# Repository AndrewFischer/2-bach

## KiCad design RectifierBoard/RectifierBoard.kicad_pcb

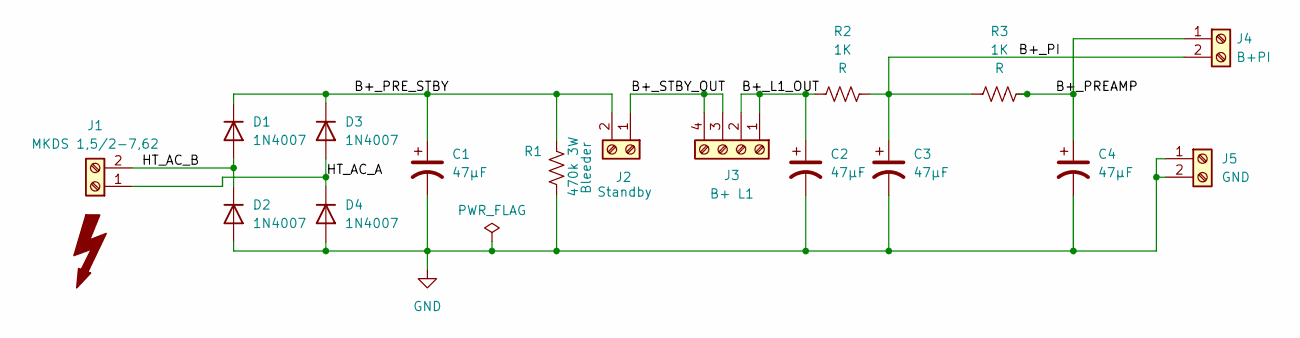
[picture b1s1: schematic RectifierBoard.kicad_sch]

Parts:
C1: 47µF; CP_Radial_D18.0mm_P7.50mm; MPN UPT2W470MHD
C2, C3, C4: 47µF; CP_Radial_D18.0mm_P7.50mm; MPN UCY2W470MHD6
D1, D2, D3, D4: 1N4007; D_DO-41_SOD81_P10.16mm_Horizontal
J1: MKDS 1,5/2-7,62; MKDS 5_2-7,62
J2: Standby; MKDS 5_2-7,62
J3: B+ L1; MKDS 5_4-7,62
J4: B+PI; MKDS 5_2-7,62
J5: GND; MKDS 5_2-7,62
R1: 470k 3W; R_Axial_DIN0617_L17.0mm_D6.0mm_P20.32mm_Horizontal; MPN FMP300FRF73-470K
R2, R3: 1K; R_Axial_DIN0617_L17.0mm_D6.0mm_P20.32mm_Horizontal

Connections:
/B+_L1_OUT: C2.1, J3.1, J3.2, R2.1
/B+_PI: C3.1, J4.2, R2.2, R3.1
/B+_PREAMP: C4.1, J4.1, R3.2
/B+_PRE_STBY: C1.1, D1.1 (K), D3.1 (K), J2.2, R1.1
/B+_STBY_OUT: J2.1, J3.3, J3.4
/HT_AC_A: D3.2 (A), D4.1 (K), J1.1
/HT_AC_B: D1.2 (A), D2.1 (K), J1.2
GND: C1.2, C2.2, C3.2, C4.2, D2.2 (A), D4.2 (A), J5.1, J5.2, R1.2; also elsewhere on the board

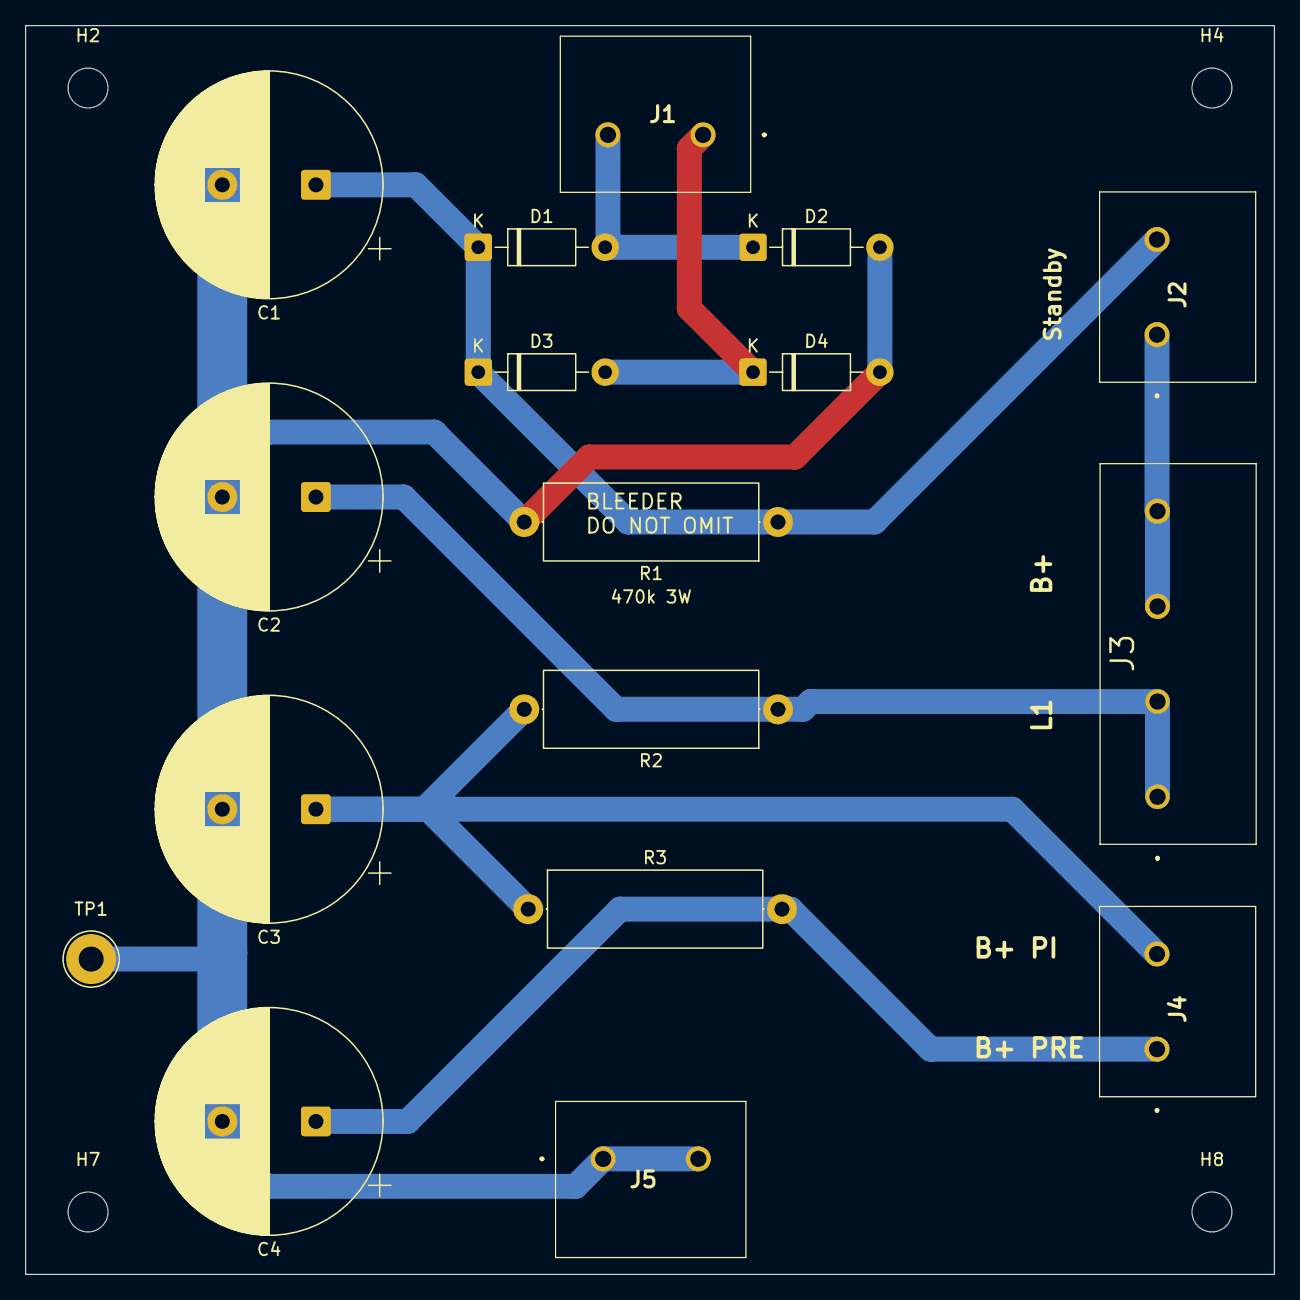
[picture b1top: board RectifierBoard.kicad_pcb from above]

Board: 2 copper layers, 100.0 x 100.0 mm, 21 parts (0 on the bottom side), 8 nets.

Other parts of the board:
H2, H4, H7, H8: M3; MountingHole_3.2mm_M3
TP1: TestPoint; TestPoint_THTPad_D4.0mm_Drill2.0mm

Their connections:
GND: TP1.1; also elsewhere on the board

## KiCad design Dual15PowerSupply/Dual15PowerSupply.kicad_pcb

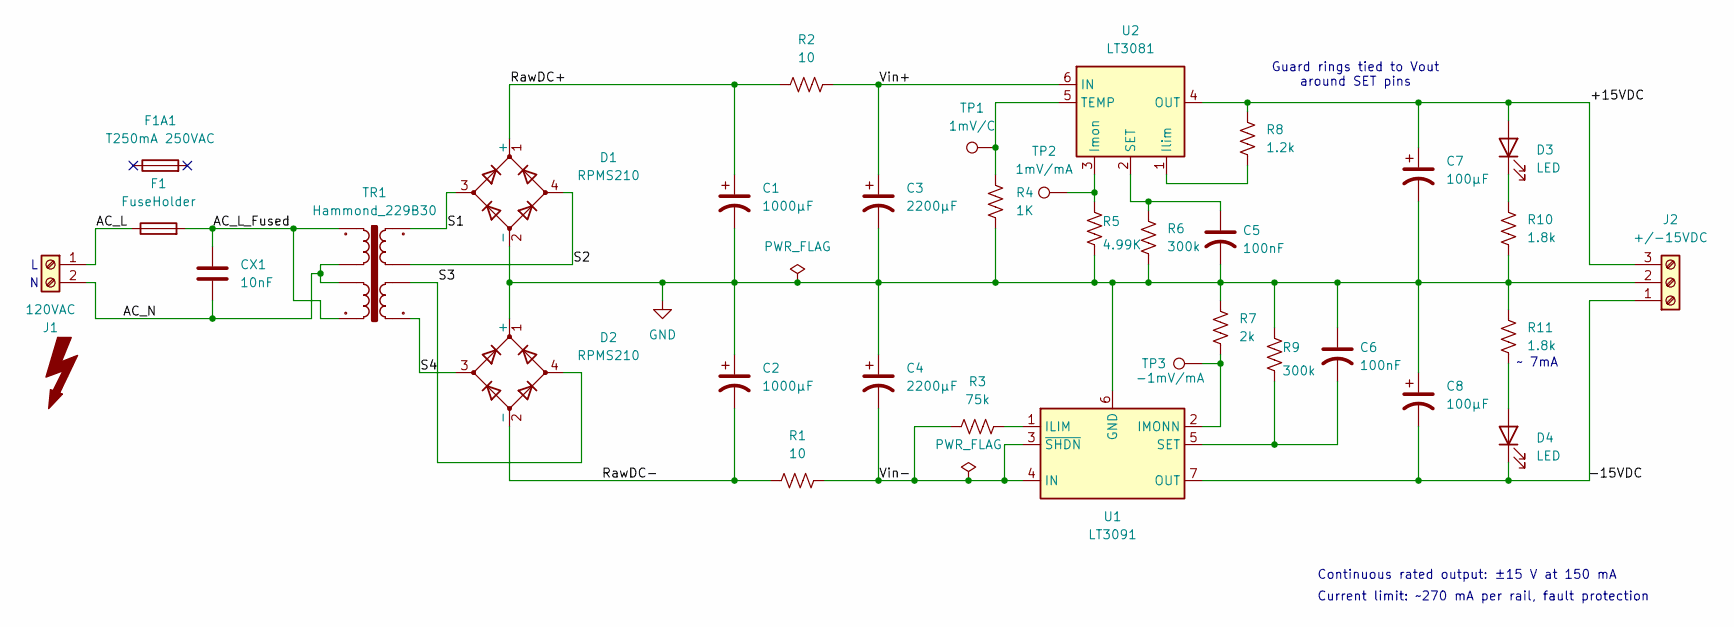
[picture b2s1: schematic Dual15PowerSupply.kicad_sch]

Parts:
C1, C2: 1000µF; CP_Radial_D12.5mm_P5.00mm; MPN EEU-FR1V102; Mouser 667-EEU-FR1V102
C3, C4: 2200µF; CP_Radial_D12.5mm_P5.00mm; MPN EEU-FR1V222L; Mouser 667-EEU-FR1V222L
C5, C6: 100nF; C_Rect_L7.2mm_W2.5mm_P5.00mm; MPN R82DC3100SH50J; Mouser 80-R82DC3100SH50J
C7, C8: 100µF; CP_Radial_D8.0mm_P3.50mm; MPN UPW1V101MPD; Mouser 647-UPW1V101MPD
CX1: 10nF; C_Rect_L13.0mm_W4.0mm_P10.00mm_FKS3_FKP3_MKS4; MPN B32921C3103M; Mouser 871-B32921C3103M
D1, D2: RPMS210; Diode_Bridge_Panjit_M4_RPMS210; MPN RPMS210_R2_00601; Mouser 241-RPMS210_R2_00601
D3, D4: LED; LED_D3.0mm; MPN LTL-4221N; Mouser 859-LTL-4221N
F1: FuseHolder; J_Wurth_WR-FSH_696105003002; MPN 696105003002; Mouser 710-696105003002
F1A1: T250mA 250VAC; MPN 0034.3111; Mouser 693-0034.3111
J1: 120VAC; PHOENIX_1731721; MPN 1731721; Mouser 651-1731721
J2: +/-15VDC; TerminalBlock_Phoenix_MKDS-3-3-5.08_1x03_P5.08mm_Horizontal; MPN 1711738; Mouser 651-1711738
R1, R2: 10; R_Axial_DIN0414_L11.9mm_D4.5mm_P20.32mm_Horizontal; MPN MOS2CT52R10R0F; Mouser 660-MOS2CT52R10R0F
R3: 75k; R_0805_2012Metric_Pad1.20x1.40mm_HandSolder; MPN RC0805FR-0775KL; Mouser 603-RC0805FR-0775KL
R4: 1K; R_0805_2012Metric_Pad1.20x1.40mm_HandSolder; MPN RT0805FRE071KL; Mouser 603-RT0805FRE071KL
R5: 4.99K; R_0805_2012Metric_Pad1.20x1.40mm_HandSolder; MPN RT0805FRD074K99L; Mouser 603-RT0805FRD074K99L
R6, R9: 300k; R_1206_3216Metric_Pad1.30x1.75mm_HandSolder; MPN RT1206BRD07300KL; Mouser 603-RT1206BRD07300KL
R7: 2k; R_1206_3216Metric_Pad1.30x1.75mm_HandSolder; MPN RT1206FRE072KL; Mouser 603-RT1206FRE072KL
R8: 1.2k; R_1206_3216Metric_Pad1.30x1.75mm_HandSolder; MPN RT1206FRE071K2L; Mouser 603-RT1206FRE071K2L
R10, R11: 1.8k; R_1206_3216Metric_Pad1.30x1.75mm_HandSolder; MPN RT1206FRE071K8L; Mouser 603-RT1206FRE071K8L
TP1: 1mV/C; TestPoint_Keystone_5005-5009_Compact_JLC; MPN 5005; Mouser 534-5005
TP2: 1mV/mA; TestPoint_Keystone_5005-5009_Compact_JLC; MPN 5005; Mouser 534-5005
TP3: -1mV/mA; TestPoint_Keystone_5005-5009_Compact_JLC; MPN 5005; Mouser 534-5005
TR1: Hammond_229B30; Hammond_229B30_RoundDrill; MPN 229B30; Mouser 546-229B30-BULK
U1: LT3091; TO-220-7_P2.54x3.7mm_StaggerOdd_Lead3.8mm_Vertical; MPN LT3091ET7; Mouser 584-LT3091ET7#PBF
U2: LT3081; TO-220-7_P2.54x3.7mm_StaggerOdd_Lead3.8mm_Vertical; MPN LT3081ET7; Mouser 584-LT3081ET7#PBF

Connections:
/+15VDC: C7.1, D3.2 (A), J2.3, R8.1, U2.4 (OUT)
/-15VDC: C8.2, D4.1 (K), J2.1, U1.7 (OUT)
/AC_L: F1.1, J1.1
/AC_L_Fused: CX1.1, F1.2, TR1.1, TR1.3
/AC_N: CX1.2, J1.2, TR1.2, TR1.4
/RawDC+: C1.1, D1.1 (+), R2.1
/RawDC-: C2.2, D2.2 (-), R1.2
/S1: D1.3, TR1.7
/S2: D1.4, TR1.8
/S3: D2.4, TR1.6
/S4: D2.3, TR1.5
/Vin+: C3.1, R2.2, U2.6 (IN)
/Vin-: C4.2, R1.1, R3.1, U1.3 (~SHDN), U1.4 (IN)
GND: C1.2, C2.1, C3.2, C4.1, C5.2, C6.1, C7.2, C8.1, D1.2 (-), D2.1 (+), J2.2, R4.2, R5.2, R6.2, R7.1, R9.1, R10.2, R11.1, U1.6 (GND)
unnamed: D3.1 (K), R10.1
unnamed: D4.2 (A), R11.2
unnamed: R3.2, U1.1 (ILIM)
unnamed: R7.2, TP3.1 (1_1), U1.2 (IMONN)
unnamed: C6.2, R9.2, U1.5 (SET)
unnamed: R8.2, U2.1 (Ilim)
unnamed: R5.1, TP2.1 (1_1), U2.3 (Imon)
unnamed: C5.1, R6.1, U2.2 (SET)
unnamed: R4.1, TP1.1 (1_1), U2.5 (TEMP)

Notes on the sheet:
~ 7mA
Current limit: ~270 mA per rail, fault protection
Continuous rated output: ±15 V at 150 mA
Guard rings tied to Vout around SET pins

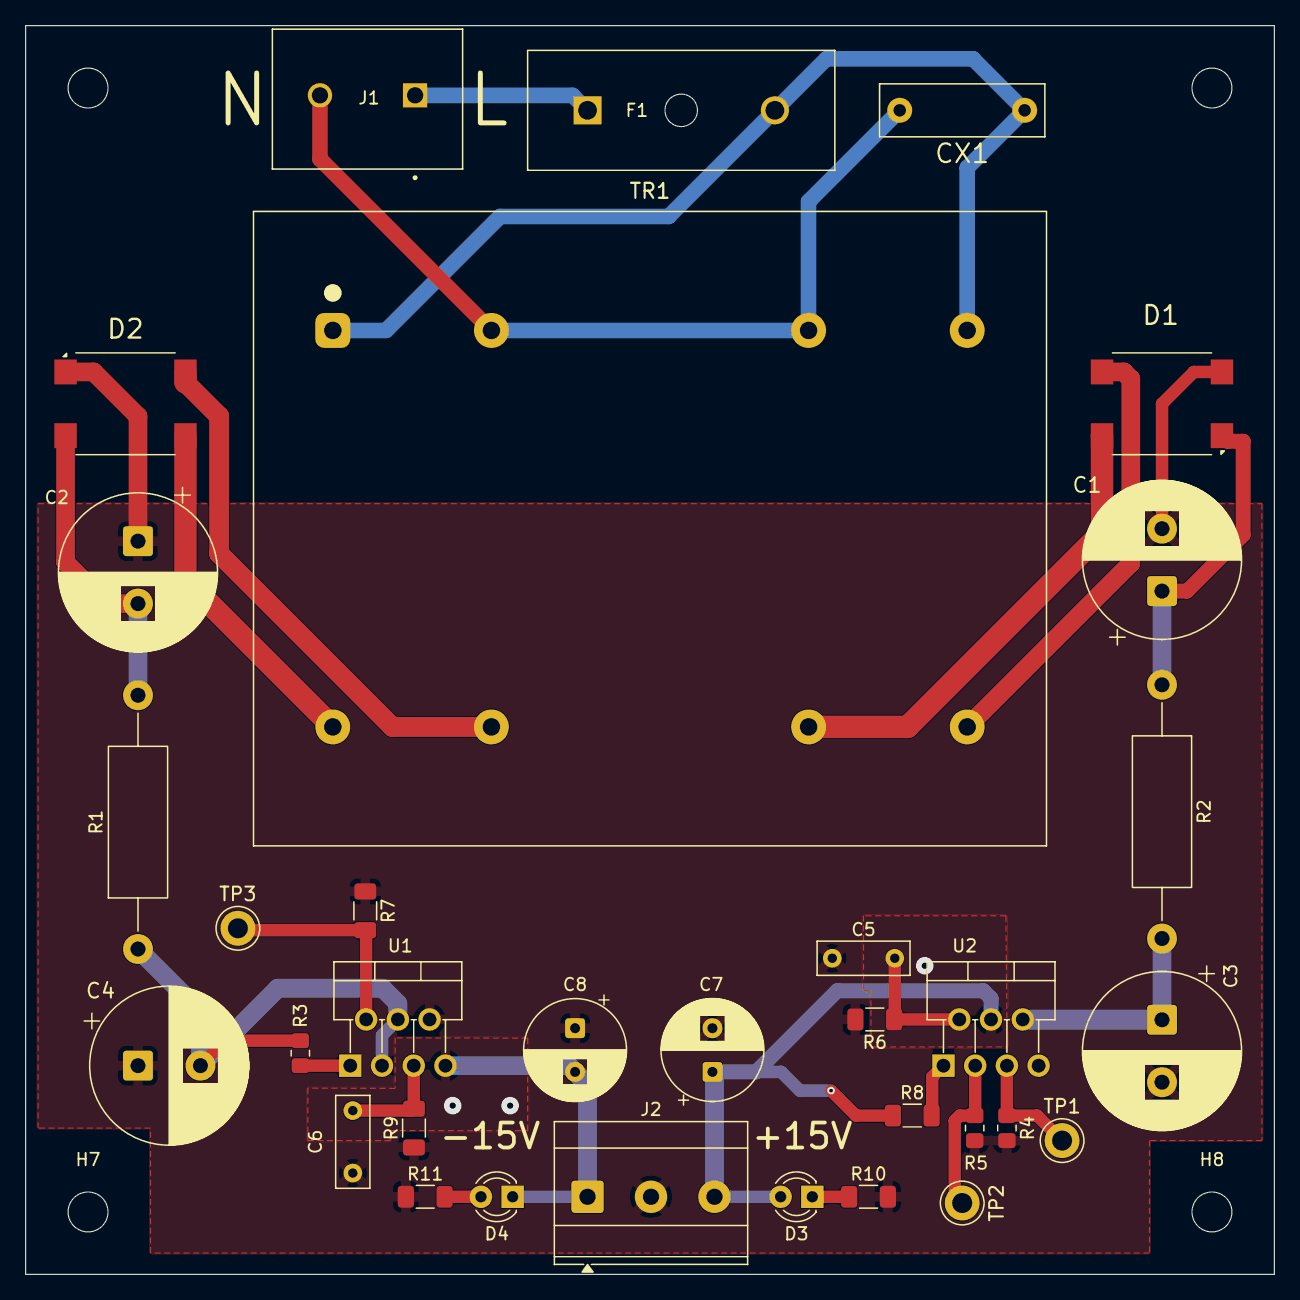
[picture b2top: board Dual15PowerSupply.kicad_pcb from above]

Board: 2 copper layers, 100.0 x 100.0 mm, 37 parts (0 on the bottom side), 23 nets.

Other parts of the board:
H2, H4, H7, H8: M3; MountingHole_3.2mm_M3

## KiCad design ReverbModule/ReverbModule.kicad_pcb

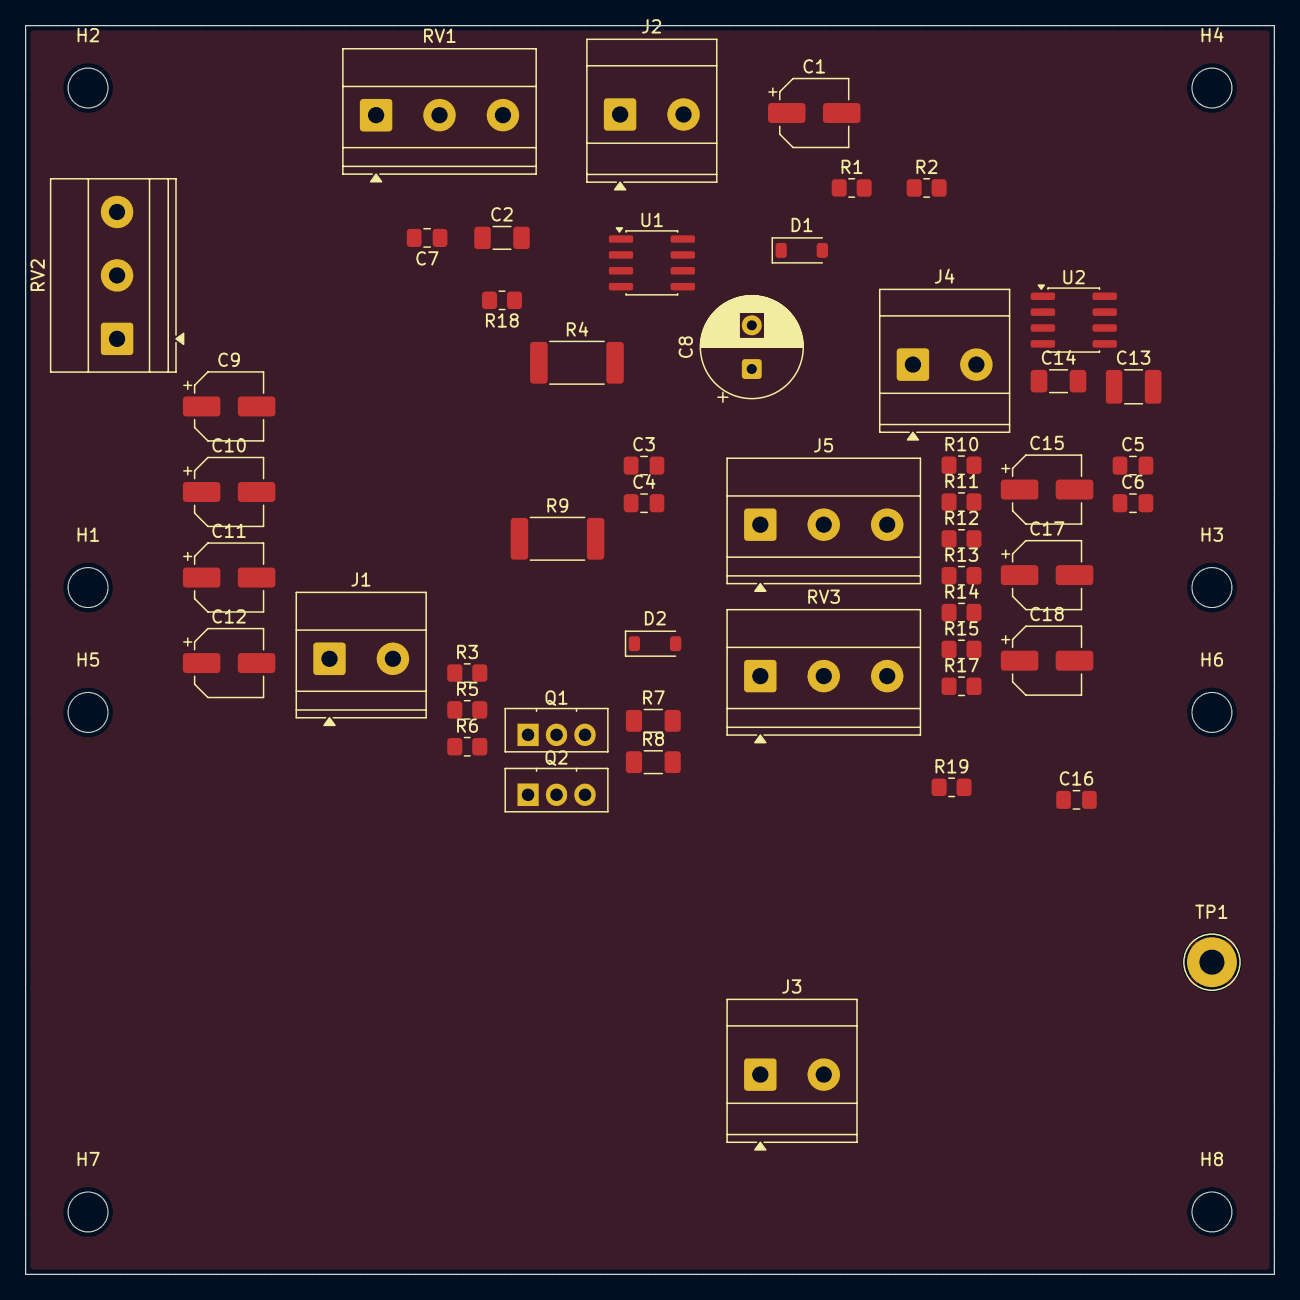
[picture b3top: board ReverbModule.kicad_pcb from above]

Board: 2 copper layers, 100.0 x 100.0 mm, 59 parts (0 on the bottom side), 29 nets, no tracks yet.

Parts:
C1, C9, C10, C11, C12, C15, C17, C18: 10µF; CP_Elec_5x5.3
C2: 2.2µF; C_1206_3216Metric_Pad1.33x1.80mm_HandSolder
C3, C4, C5, C6, C7: 100nF; C_0805_2012Metric_Pad1.18x1.45mm_HandSolder
C8: 100µF; CP_Radial_D8.0mm_P3.50mm
C13: 100nF; C_1210_3225Metric_Pad1.33x2.70mm_HandSolder
C14: 10nF; C_1206_3216Metric_Pad1.33x1.80mm_HandSolder
C16: 220p; C_0805_2012Metric_Pad1.18x1.45mm_HandSolder
D1, D2: 1N4148W; D_SOD-123
H1, H2, H3, H4, H5, H6, H7, H8: M3; MountingHole_3.2mm_M3
J1: Tank; TerminalBlock_Phoenix_MKDS-1,5-2-5.08_1x02_P5.08mm_Horizont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
J2, J4: Screw_Terminal_01x02; TerminalBlock_Phoenix_MKDS-3-2-5.08_1x02_P5.08mm_Horizontal
J3: Foot_Switch; TerminalBlock_Phoenix_MKDS-3-2-5.08_1x02_P5.08mm_Horizontal
J5: Screw_Terminal_01x03; TerminalBlock_Phoenix_MKDS-1,5-3-5.08_1x03_P5.08mm_Horizont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
Q1: BD139; TO-126-3_Vertical
Q2: BD140; TO-126-3_Vertical
R1, R2, R3, R19: 10k; R_0805_2012Metric_Pad1.20x1.40mm_HandSolder
R4: 33; R_2512_6332Metric_Pad1.40x3.35mm_HandSolder
R5: 6.8k; R_0805_2012Metric_Pad1.20x1.40mm_HandSolder
R6: 6k8; R_0805_2012Metric_Pad1.20x1.40mm_HandSolder
R7, R8: 10; R_1206_3216Metric_Pad1.30x1.75mm_HandSolder
R9: 150; R_2512_6332Metric_Pad1.40x3.35mm_HandSolder
R10: 4.7k; R_0805_2012Metric_Pad1.20x1.40mm_HandSolder
R11: 100k; R_0805_2012Metric_Pad1.20x1.40mm_HandSolder
R12: 560R; R_0805_2012Metric_Pad1.20x1.40mm_HandSolder
R13: 220; R_0805_2012Metric_Pad1.20x1.40mm_HandSolder
R14, R17: 22k; R_0805_2012Metric_Pad1.20x1.40mm_HandSolder
R15: 560; R_0805_2012Metric_Pad1.20x1.40mm_HandSolder
R18: 20K; R_0805_2012Metric_Pad1.20x1.40mm_HandSolder
RV1: 10k; TerminalBlock_Phoenix_MKDS-1,5-3-5.08_1x03_P5.08mm_Horizont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
RV2: 20k; TerminalBlock_Phoenix_MKDS-1,5-3-5.08_1x03_P5.08mm_Horizont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
RV3: 10K; TerminalBlock_Phoenix_MKDS-1,5-3-5.08_1x03_P5.08mm_Horizont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
TP1: TestPoint; TestPoint_THTPad_D4.0mm_Drill2.0mm
U1, U2: NE5532; SOIC-8_3.9x4.9mm_P1.27mm

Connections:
+15V: C3.1, C5.1, C11.1, J5.1, Q1.2 (C), R5.1, U1.8 (V+), U2.8 (V+)
-15V: C4.2, C6.2, C12.2, J5.3, Q2.1 (E), R6.2, U1.4 (V-), U2.4 (V-)
/Driver/Q1B: C9.1, D1.2 (A), Q1.3 (B), R5.2
/Driver/Q2B: C9.2, C10.1, D1.1 (K), D2.2 (A), J1.1 (In1), R7.2, R8.1, R9.1, U1.7
/Driver/TankIn-: C8.1, J1.2 (Ext1), R4.1
Dry: R18.2, R19.1, RV3.2, U2.2 (-)
GND: C3.2, C4.1, C5.2, C6.1, C11.2, C12.1, C15.2, J2.1, J3.2, J4.2, J5.2, R3.1, R4.2, R10.2, R11.2, R17.1, RV1.3, RV2.3, RV3.3, TP1.1, U1.3 (+), U2.3 (+)
unnamed: C1.2, R1.1
unnamed: C2.1, R2.2, U1.1
unnamed: C2.2, R18.1, RV1.1
unnamed: C7.1, RV1.2
unnamed: C7.2, RV2.1
unnamed: C13.1, C14.1, R11.1, R12.1
unnamed: C14.2, R10.1
unnamed: C15.1, R13.2
unnamed: C16.2, R14.2, R15.1, U2.7
unnamed: C17.2, R15.2
unnamed: C18.2, R19.2, U2.1
unnamed: C10.2, D2.1 (K), Q2.3 (B), R6.1
unnamed: C1.1, J2.2
unnamed: C17.1, J3.1, RV3.1
unnamed: C18.1, J4.1, R17.2
unnamed: Q1.1 (E), R7.1
unnamed: Q2.2 (C), R8.2
unnamed: R1.2, R2.1, U1.2 (-)
unnamed: R3.2, RV2.2, U1.5 (+)
unnamed: C8.2, R9.2, U1.6 (-)
unnamed: R12.2, U2.5 (+)
unnamed: C16.1, R13.1, R14.1, U2.6 (-)

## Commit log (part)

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2026-05-24 Initial schematic entry
    Lets get started
2026-05-24 .OP works
    .OP works - Power stage initial DC operation ok.
2026-05-25 PI and output appear to work
    First pass for output stage that looks ok in spice.
2026-05-25 PowerSupply start
2026-06-13 Add Rectifier PCB
2026-06-14 First cut at PCB layout
2026-06-14 Layout - CORRECT GROUND ISSUE NEXT !!!!
2026-06-15 Getting closer
2026-06-19 Good stuff
2026-06-20 In work
2026-06-20 In progress
2026-06-21 added more parts
2026-06-22 In worl
2026-06-22 More Schematic Capture
2026-06-26 Schematic Capture
2026-06-26 Capture Complete
2026-06-28 ub wirj
2026-06-29 Regulator Design
